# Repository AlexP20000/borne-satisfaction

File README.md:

# The project #
This french project consists of making a terminal with 3 push buttons that can record the supports on an SD card to collect results for a satisfaction survey.

You can found the project's page on [wikifactory](https://wikifactory.com/+uboopenfactory/borne-de-satisfaction)

Last : most of the documentation is written in French...

# Directory structure #

## Electronique
You can found here the Eagles project and everything about the mother board constuction.

## Mécanique
You can found here everything about the constuction of the wood-box as Lasercut plans.

Plans are on SVG format.

## Programmation
This is the place where you will found the main program, tests and everything about the ESP-32 code.

Code is written in C++ Language for a Firebeetle ESP32. Please [check the documentation before compiling](./Programmation/Microcontroleur/README.md).

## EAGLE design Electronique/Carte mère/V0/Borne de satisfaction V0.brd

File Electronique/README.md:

L'électronique de la borne de satisfaction s'articule autour de l'architecture composée :
- Une carte Firebeetle ESP32 (Processeur+Charge de la batterie) <br>
*3 Boutons poussoirs pour le vote
*3 LEd pour indiquer le bouton pressé
*Un lecteur de carte SD et sa carte SD qui contient les résultats des votes
*Une horloge temps réelle pour indiquer l'horodatage des votes

### Architecture Principale ###

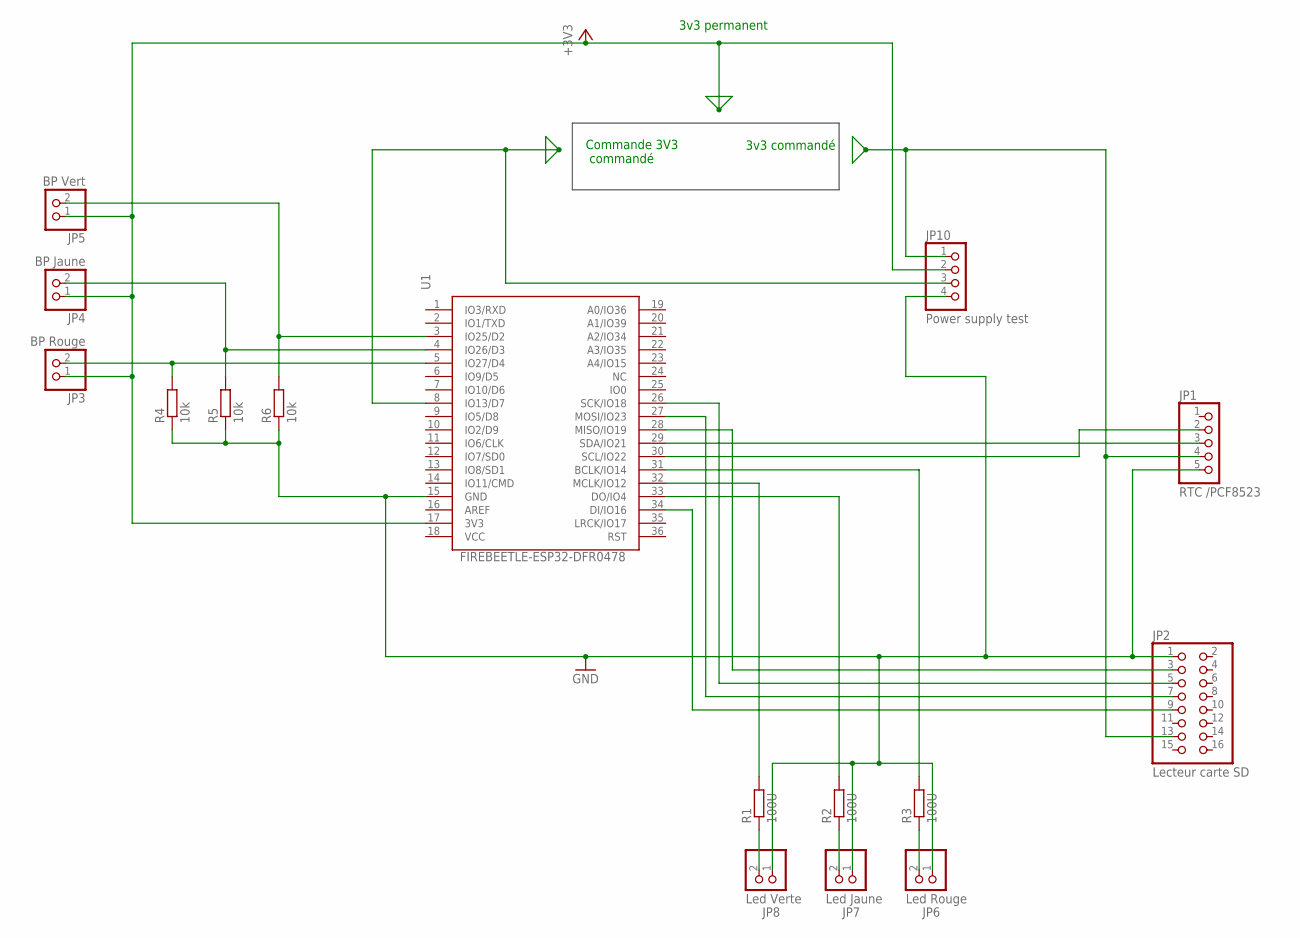
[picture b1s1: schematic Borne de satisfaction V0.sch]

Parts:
JP1: RTC /PCF8523; 1X05
JP2: Lecteur carte SD; 2X08
JP3: BP Rouge; 1X02
JP4: BP Jaune; 1X02
JP5: BP Vert; 1X02
JP6: Led Rouge; 1X02
JP7: Led Jaune; 1X02
JP8: Led Verte; 1X02
JP10: Power supply test; 1X04
R1, R2, R3: 100U; 0207/10
R4, R5, R6: 10k; 0207/10
U1: FIREBEETLE-ESP32-DFR0478; FIREBEETLE_ESP32

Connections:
+3V3: JP3.1, JP4.1, JP5.1, JP10.2, U1.17 (3V3)
GND: JP1.5, JP2.1, JP6.1, JP7.1, JP8.1, JP10.4, R4.1, R5.1, R6.1, U1.15 (GND)
unnamed: JP10.3, U1.8 (IO13/D7)
unnamed: JP2.3, U1.28 (MISO/IO19)
unnamed: JP2.5, U1.26 (SCK/IO18)
unnamed: JP2.7, U1.27 (MOSI/IO23)
unnamed: JP2.9, U1.34 (DI/IO16)
unnamed: JP1.4, JP2.13, JP10.1
unnamed: JP3.2, R4.2, U1.5 (IO27/D4)
unnamed: JP1.2, U1.30 (SCL/IO22)
unnamed: JP1.3, U1.29 (SDA/IO21)
unnamed: JP8.2, R1.1
unnamed: JP7.2, R2.1
unnamed: JP6.2, R3.1
unnamed: R1.2, U1.32 (MCLK/IO12)
unnamed: R3.2, U1.31 (BCLK/IO14)
unnamed: R2.2, U1.33 (DO/IO4)
unnamed: JP4.2, R5.2, U1.4 (IO26/D3)
unnamed: JP5.2, R6.2, U1.3 (IO25/D2)

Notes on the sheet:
3v3 commandé
Commande 3V3 commandé
3v3 permanent

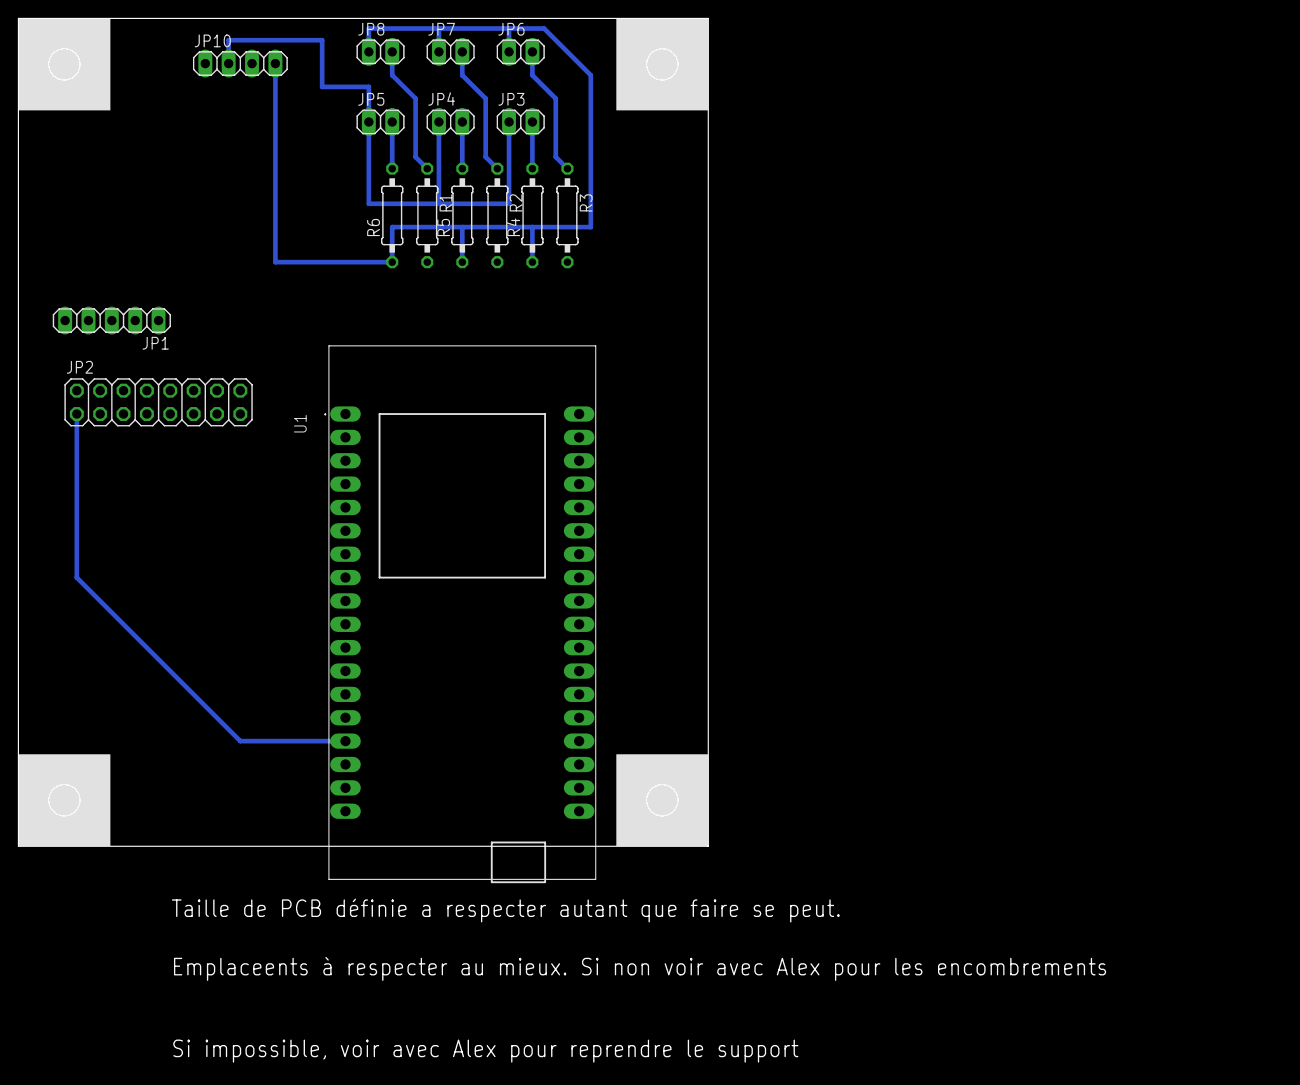
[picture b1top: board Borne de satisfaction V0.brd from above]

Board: 2 copper layers, 75.0 x 90.0 mm, 16 parts (0 on the bottom side), 19 nets.

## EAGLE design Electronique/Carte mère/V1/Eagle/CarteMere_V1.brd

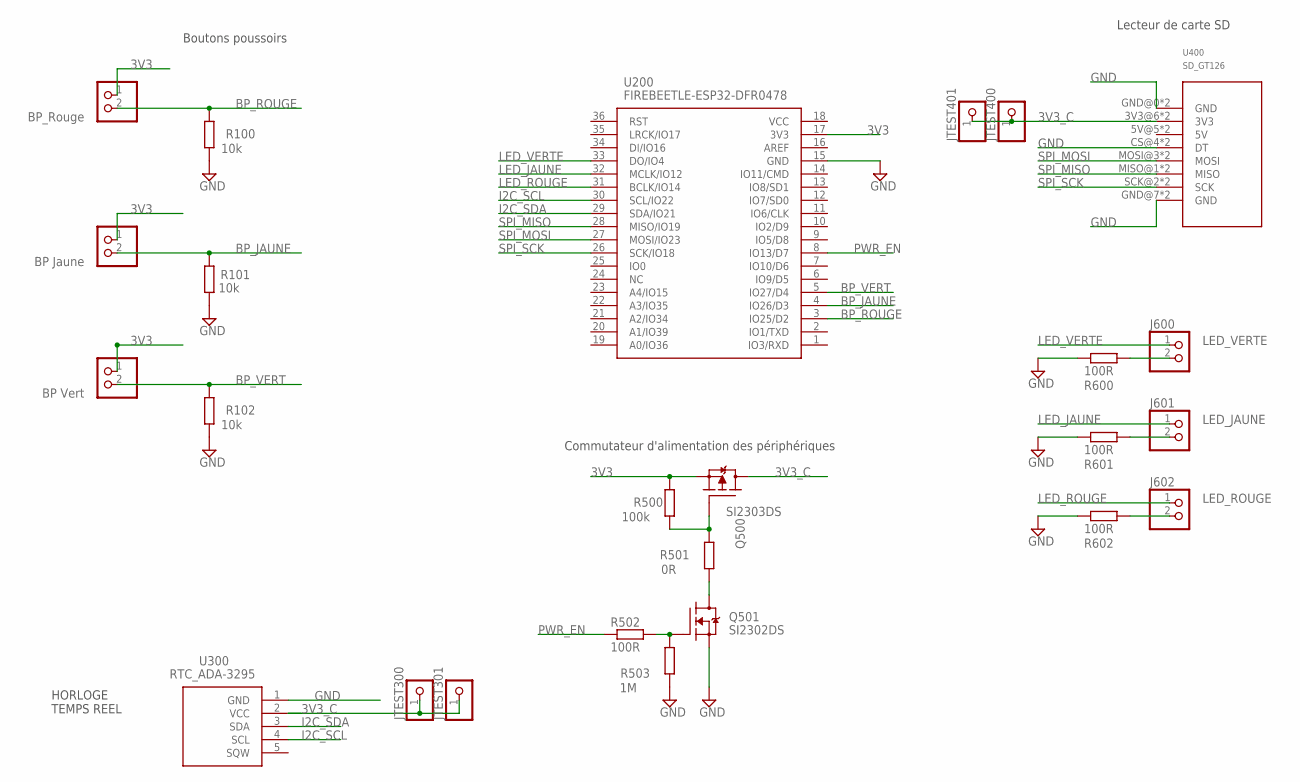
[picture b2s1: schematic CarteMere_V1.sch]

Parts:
J100: BP_Rouge; 1X02
J101: BP Jaune; 1X02
J102: BP Vert; 1X02
J600: LED_VERTE; 1X02
J601: LED_JAUNE; 1X02
J602: LED_ROUGE; 1X02
JTEST300, JTEST301, JTEST400, JTEST401: PINHD-1X1; 1X01
Q500: SI2303DS; SOT23
Q501: SI2302DS; SOT23
R100, R101, R102: 10k; 0207/10
R500: 100k; 0207/10
R501: 0R; 0207/10
R502, R600, R601, R602: 100R; 0207/10
R503: 1M; 0207/10
U200: FIREBEETLE-ESP32-DFR0478; FIREBEETLE_ESP32
U300: RTC_ADA-3295; ADA3295
U400: SD_GT126

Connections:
3V3: J100.1, J101.1, J102.1, Q500.2 (S), R500.2, U200.17 (3V3)
3V3_C: JTEST300.1, JTEST301.1, JTEST400.1, JTEST401.1, Q500.3 (D), U300.2 (VCC), U400.3V3@6 (3V3), U400.3V3@9 (3V3)
BP_JAUNE: J101.2, R101.2, U200.4 (IO26/D3)
BP_ROUGE: J100.2, R100.2, U200.3 (IO25/D2)
BP_VERT: J102.2, R102.2, U200.5 (IO27/D4)
DQ501: Q501.3 (D), R501.1
GND: Q501.2 (S), R100.1, R101.1, R102.1, R503.1, R600.1, R601.1, R602.1, U200.15 (GND), U300.1 (GND), U400.CS@4 (DT), U400.CS@11 (DT), U400.GND@0 (GND), U400.GND@7 (GND), U400.GND@8 (GND), U400.GND@15 (GND)
I2C_SCL: U200.30 (SCL/IO22), U300.4 (SCL)
I2C_SDA: U200.29 (SDA/IO21), U300.3 (SDA)
LED_JAUNE: J601.1, U200.32 (MCLK/IO12)
LED_ROUGE: J602.1, U200.31 (BCLK/IO14)
LED_VERTE: J600.1, U200.33 (DO/IO4)
unnamed: Q501.1 (G), R502.2, R503.2
unnamed: J600.2, R600.2
unnamed: J601.2, R601.2
unnamed: J602.2, R602.2
unnamed: Q500.1 (G), R500.1, R501.2
PWR_EN: R502.1, U200.8 (IO13/D7)
SPI_MISO: U200.28 (MISO/IO19), U400.MISO@1 (MISO), U400.MISO@14 (MISO)
SPI_MOSI: U200.27 (MOSI/IO23), U400.MOSI@3 (MOSI), U400.MOSI@12 (MOSI)
SPI_SCK: U200.26 (SCK/IO18), U400.SCK@2 (SCK), U400.SCK@13 (SCK)

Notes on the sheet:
HORLOGE TEMPS REEL
Commutateur d'alimentation des périphériques
Lecteur de carte SD
Boutons poussoirs

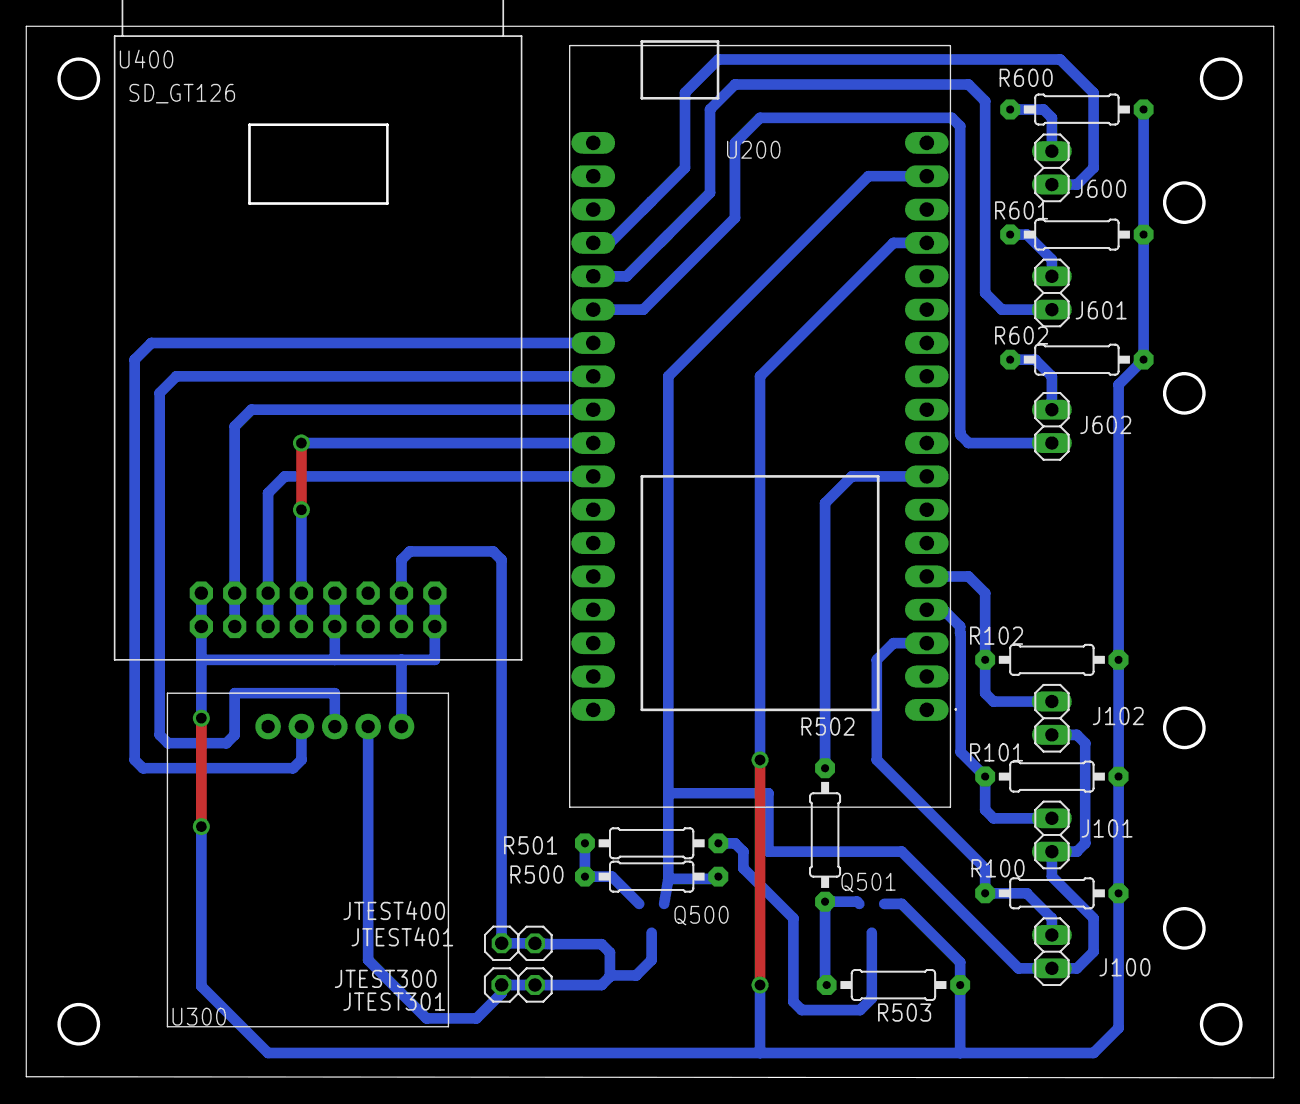
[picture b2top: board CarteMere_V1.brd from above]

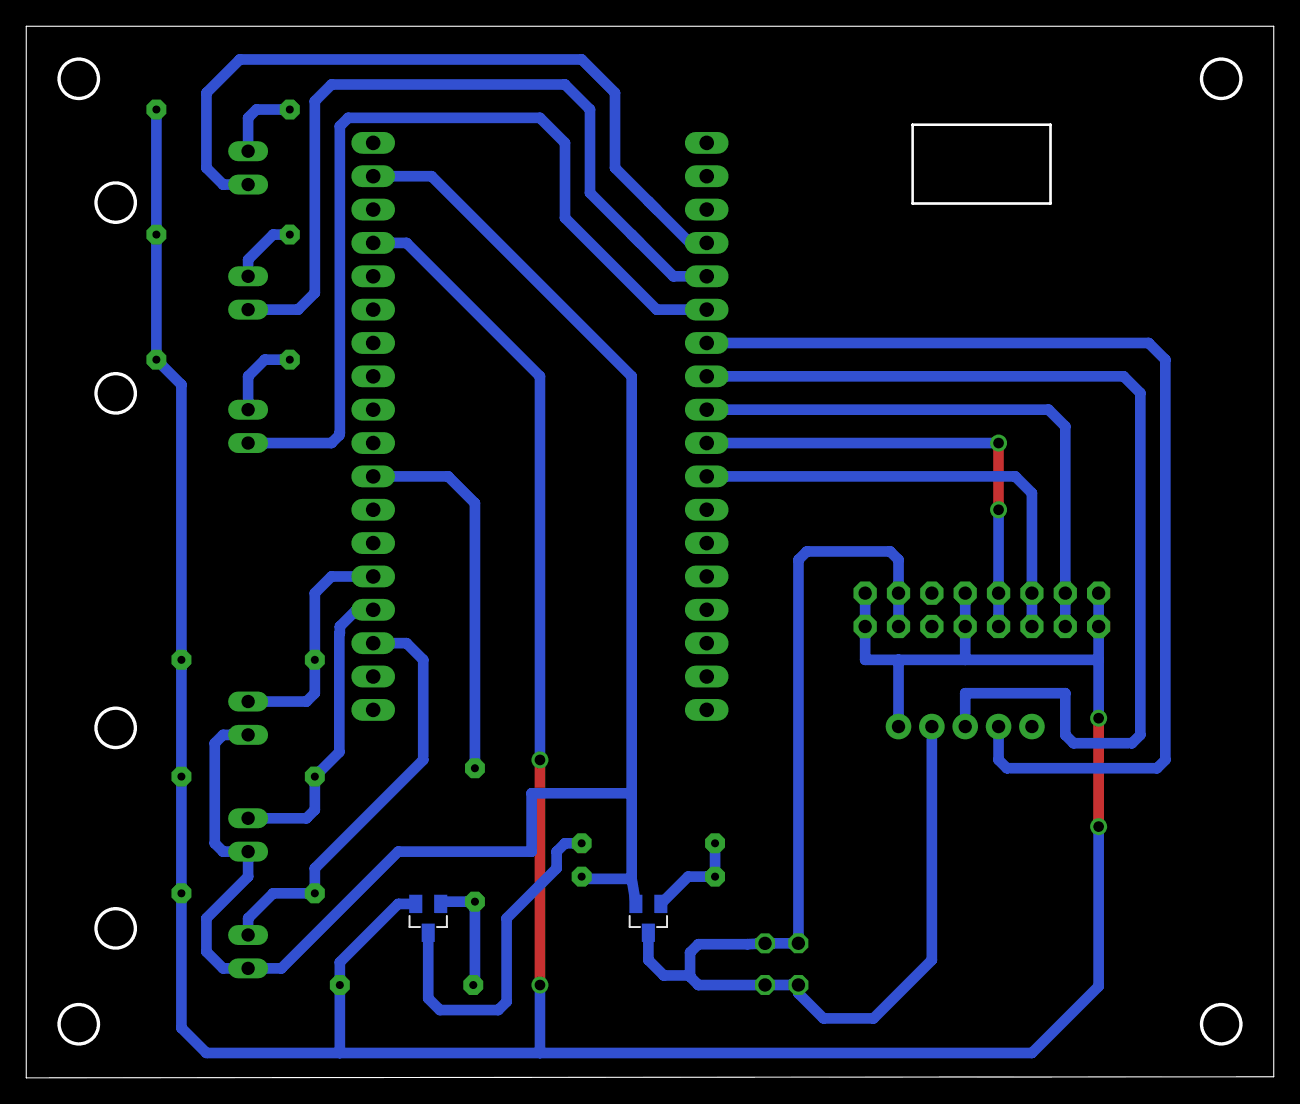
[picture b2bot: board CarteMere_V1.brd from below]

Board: 2 copper layers, 95.0 x 80.1 mm, 25 parts (2 on the bottom side), 21 nets.

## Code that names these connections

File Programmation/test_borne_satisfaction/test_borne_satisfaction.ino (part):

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#define ON HIGH
#define OFF LOW

#define PIN_LED_VERTE 4
#define PIN_LED_JAUNE 12
#define PIN_LED_ROUGE 14

#define PIN_BP_VERT 27
#define PIN_BP_JAUNE 26
#define PIN_BP_ROUGE 25

#define PIN_PWR_EN 13

#define TIMEOUT_TEST_BP 10000 // en ms

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  delay(100);

  // initialisation des E/S
  pinMode (PIN_LED_VERTE,OUTPUT);
  pinMode (PIN_LED_JAUNE,OUTPUT);
  pinMode (PIN_LED_ROUGE,OUTPUT);
  led(VERT,OFF);
  led(JAUNE,OFF);
  led(ROUGE,OFF);
  
  pinMode (PIN_BP_VERT,INPUT);
  pinMode (PIN_BP_JAUNE,INPUT);
  pinMode (PIN_BP_ROUGE,INPUT);

  pinMode(PIN_PWR_EN,OUTPUT);
  peripheriques(OFF);
  
  // début du test
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    debut = millis();
    res=false;
    while (millis() - debut < TIMEOUT_TEST_BP) {
      if (digitalRead(PIN_BP_VERT) == HIGH) {
        res=true;
        break;
      }
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    debut = millis();
    res=false;
    while (millis() - debut < TIMEOUT_TEST_BP) {
      if (digitalRead(PIN_BP_JAUNE) == HIGH) {
        res=true;
        break;
      }
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    debut = millis();
    res=false;
    while (millis() - debut < TIMEOUT_TEST_BP) {
      if (digitalRead(PIN_BP_ROUGE) == HIGH) {
        res=true;
        break;
      }
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}

void led( byte couleur, bool etat) {
  if (couleur == VERTE) digitalWrite (PIN_LED_VERTE,etat);
  if (couleur == VERT)  digitalWrite (PIN_LED_VERTE,etat);
  if (couleur == JAUNE) digitalWrite (PIN_LED_JAUNE,etat);
  if (couleur == ROUGE) digitalWrite (PIN_LED_ROUGE,etat);
}

void peripheriques(bool etat) {
  // alimentation des périphériques
  digitalWrite(PIN_PWR_EN,etat);
  delay(20); // pour laisser à l'alimentation le temps de s'établir 20 ms mini
  if (etat) {
    Serial.println ("Alimentation des périphériques ON");
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
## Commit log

2022-02-09 Boitiers
2022-02-09 Documentation
2022-02-09 Renommage répertoire
2022-02-09 Modification plaque avant
2022-02-09 Version plus grande
2022-02-09 Ajustement emplacement carte mère
2022-02-10 Structure du projet
2022-02-22 Restructuration des répertoires
2022-02-24 Changement des dimensions
2022-02-25 Mise à jour fichiers carte mère et schéma block
2022-02-25 Mise à jour GERBER
2022-02-25 maj README Elec
2022-02-25 maj readme
2022-02-25 Reprise de la boite
2022-02-25 Rangement des pièces pour optimisation de la découpe
2022-02-28 Modification de l'emboitements
2022-02-28 Modification du capot
2022-02-28 Ajout des légendes
2022-03-01 Programme de test de la carte mère
    Version 1.0
2022-03-01 Mise à jour des Readme
2022-03-02 Re-nomer le répertoire CarteMere->Eagle
    Renomer l'ancien Crte Mere en répertoire EAGLE
2022-03-03 Mise à jour des paramètres des matériaux
2022-03-04 Mise à jour de l'algorythme
2022-03-04 Mise à jour de l'algo
2022-03-07 Update README.md
    Suppression de la programmation
2022-03-07 Squelette des tests
2022-03-07 Mesure batterie level en pourcentage
2022-03-07 Ajout des librairies pour lire/écrire sur carte SD
2022-03-07 Cause du wake up
2022-03-07 Accès aux fichiers de la carte SD
2022-03-07 Fonction d'écriture du fichier param.ini
2022-03-07 Intégration du deep sleep
2022-03-08 insertion des logos
    logo lego et maison du bio
2022-03-08 Faces avant
2022-03-08 Modification logos
2022-03-08 Modification des largeur de trou de boutons
2022-03-08 Plaque PMMA
2022-03-08 Modification des longuer des mortaises
2022-03-08 Mise à jour des puissance de gravage
2022-03-08 Librairie iniFile
2022-03-08 Installation de la carte ESP32
2022-03-08 Modification arborescences pour avoir les librairies dépendantes en locale
2022-03-08 Renommage des fonctions du fichier cartesSD.h pour conformités nomenclature
2022-03-08 Mise à jour de la carte à choisir pour la compilation
2022-03-08 Test : Deep sleep
2022-03-08 Test unitaire des leds
2022-03-08 Renommage des PIN
2022-03-08 Tests sur tout les matériels
2022-03-08 test unitaire carte SD
2022-03-08 Ecriture du fichier de config
2022-03-08 Mise en deep sleep et réveille par les boutons
2022-03-08 Lecture du ficheir ini (mais ca ne marche pas)
2022-03-09 Ajout calle pour carte SD
2022-03-09 ajout trou pour maintien Carte SD
2022-03-09 Modif dimension ligne alim
2022-03-09 Ajout support de carte SD
2022-03-09 Installation de la carte FireBeetle-ESP32
2022-03-09 Librairies spécifiques pour le projet
2022-03-09 Ajout de commentaires dans le code
2022-03-09 mise à jour carte mère
2022-03-09 Lecture des valeurs dans le fichier ini
2022-03-09 Mise hors tension des périphériques
2022-03-09 Construction de la ligne pour le fichier csv des mesures
2022-03-09 Ajout de la librairie RTClib
2022-03-09 Mise à jour des mesures
2022-03-10 Installation de LittleFS
2022-03-10 Test littelFS
2022-03-10 A finir
2022-03-10 Finir la partie de sauvegarde de la synthese en ROM
2022-03-10 Test : LittleFS
2022-03-10 Installation de llittleFS
2022-03-10 Ecriture de la synthese dans le file system de la ROM
2022-03-10 Simplification du code
2022-03-10 Test : RTC V2
2022-03-10 TEST : Mise à l'heure de la RTC via server NTP
2022-03-10 Passage en pre-prod
2022-03-11 Déplacement des logos dans le répertoire
2022-03-11 Ajout d'une cage pour la carte mère
2022-03-11 Déplacement de la partie pour mode debug
2022-03-11 Mise à l'heure de la RTC
2022-03-11 Mise en place d'un bouchon sur la batterie (renvoie toujours 100%)
2022-03-11 Initialisation bidon du niveau de la batterie
2022-03-11 Formattage du littleFS au démarrage
2022-03-14 Modification du diagramme
2022-03-15 Modificaiton du diamètre perçage vis et recréation des fichiers gerbers
2022-03-15 Modif Routage Bottom
2022-03-17 Create Support question.svg
    Proposition de support de question et plaque obstructrice.
2022-03-22 Supression des fichiers DS_Store
2022-03-22 MOdificaiton du Giignore pour ne plus prendre en compte les fichier DS_store
2022-03-22 Séparation des pièces pour découpe simplifiée
2022-03-22 Agrandissement et solidification de la fente pour panneau affichage A4 + Déplacement des troudes boutons & leds
2022-03-22 Ajout de "face intérieur" sur la pice tenant l'interrupteur
2022-03-22 Suppression tenon de la pice tenant l'interrupteur
2022-03-22 Modificaitons de l'emplacement des tasseaux
2022-03-22 Instructions pour l'utilisation de deepnest
2022-03-22 Mise à jour de la documentation du projet
2022-03-22 Installation des librairies
2022-03-22 Simplificaiton de la documentation
2022-04-04 Plan pour découpe à la CNC
2022-04-05 Add second in time format (issue #7)
2022-04-05 Change file's names (issue #9)
2022-04-05 Optimisation de la compilation (issue #4)
2022-04-05 Renvoie le bon niveau de batterie
2022-04-05 Initialisaiton du fichier de la question lors du formatage de llittleFS
2022-04-05 Mise à jour alogorythme pour initialisaiton de LittleFS
2022-04-05 Passage en prod
2022-04-05 Mise à jour documentation du programme
2022-04-05 Déplacement de variable globale
2022-04-05 Documentation du code
2022-04-06 Modifications de la fente de la carte SD
2022-04-06 Agencement pour CNC
2022-04-06 Jonction des chemins
2022-04-06 Agencement pour usinage CNC
2022-04-07 Ajustement pour découpe CNC
2022-04-07 Création gabarit de gravage
2022-04-07 Ajout logos Europeen + intereg
2022-04-07 Ajout logos
2022-04-08 Gabarit de gravage des plaques
2022-04-08 Modification des valeurs de gravage
2022-04-08 Protection contre des valeurs négatifs du pourcentage (si < 0, on renvoie 0 )
2022-04-15 Inversion des alertes lumineuses (problème carte SD = rouge)
2022-04-15 Modification gabarit pour avoir 2eme face avant
2022-04-26 Issue 10 : Protection des valeurs de pourcentage de niveau de batterie
2022-04-26 Initialisation de la date et l'heure à partir du fichier ini (issue 11)
2022-04-27 Issue 14 : Lecture de l'année, mois, jou, heure et minutes à partir du fichier de configuration
2022-04-27 Traces de debug
2022-04-27 Issue 11
2022-04-27 Mise à jour algo
2022-04-27 ConfiguraitonConfig pour Visual Studio Code
2022-04-27 Passage en mode prod
2022-04-27 Tran,sfert des variables dans la partie initialisation.h
2022-04-29 Issue 16
2022-04-29 Issue 15 : Orthographe
2022-04-29 Mise à jour de la documentation
2022-05-02 Issue 18 : Vérification de la validité des date et heure saisie
2022-05-02 Gestion de la boucle infinie des alarmes
2022-05-02 Passage en production (mise en commentaire des traces)
2022-05-02 Renommage de la variable du timer
2022-05-03 Update Batterie.h
    Modification des min et max pour la batterie
2022-05-09 Issue #19 : Fautes d'orthographe dans fichier ini
2022-05-10 Issue #22 : Tension batterie
    Correction du clignottement de la LED jaune en fonction de la tension de la batterie.
2022-05-10 Utilisation d'un numéro de version pour le code.
2022-05-10 Generation de la documentation Doxygen
2022-05-10 Mise à jour de l'algo pour que le problème de batterie ne soit pas bloquant
2022-05-10 Suprpession fichier innutil
2022-05-10 Config workspace de VSC
2022-05-10 issue #23 : Protection contre une année < 2000
2022-05-10 Commentaires dans le code
2022-05-10 Protection contre l'arrachement de la carte SD
2022-05-11 Modif test date
2022-05-11 Ajout de traces
2022-05-11 Ajout de delay
2022-05-11 Réduction des delais
2022-05-11 issue #23 : Mise à jour des champs date + heure
2022-05-12 Orthographe
2022-05-12 Réorganisation programmes de test
2022-05-13 Fichier Eagle pour Carte mère
2022-05-13 Documentation technique du code C++
2022-05-17 Update README.md
    Correction de fautes
2022-06-29 Ajout des notices d'assemblage et montage (FR/UK)
2022-06-29 Mise à jour documentation

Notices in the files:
Programmation/test_borne_satisfaction/test_borne_satisfaction.ino:
License : CC - BY - SA
